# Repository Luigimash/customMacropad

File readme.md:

# Custom Macropad

A completely custom-built customizable macropad I built as a gift for a friend. Completed officially on March 11 2024.

Features:
- 3D printed enclosure
- Laser cut 1.5mm acrylic plate
- Custom PCB 
- QMK VIAL firmware 

All of my design files are collected within this repository. Some other items that you may need to purchase to complete this build:
- Standard Mechanical Keyboard Switches with a CherryMX footprint (used Wuque Studio Browns)
- SEED XIAO RP2040 Microcontroller
- 1N4148 Small Signal Switching Diodes
- EC11 (used Alps EC11E15244B2-ND)

Some tools I used:
- 3D Printers
- Laser Cutters
- AutoCAD for designing the acrylic plate
- Solidworks for designing the enclosure
- KiCAD for the circuit schematic and PCB gerbers

## Gallery

## Next Steps
- The rotary encoders are WAY too close to the keycaps, making it difficult to rotate (although it does thankfully actually rotate). They should be moved such that they are placed further away from the keycaps by at least 5mm or so.

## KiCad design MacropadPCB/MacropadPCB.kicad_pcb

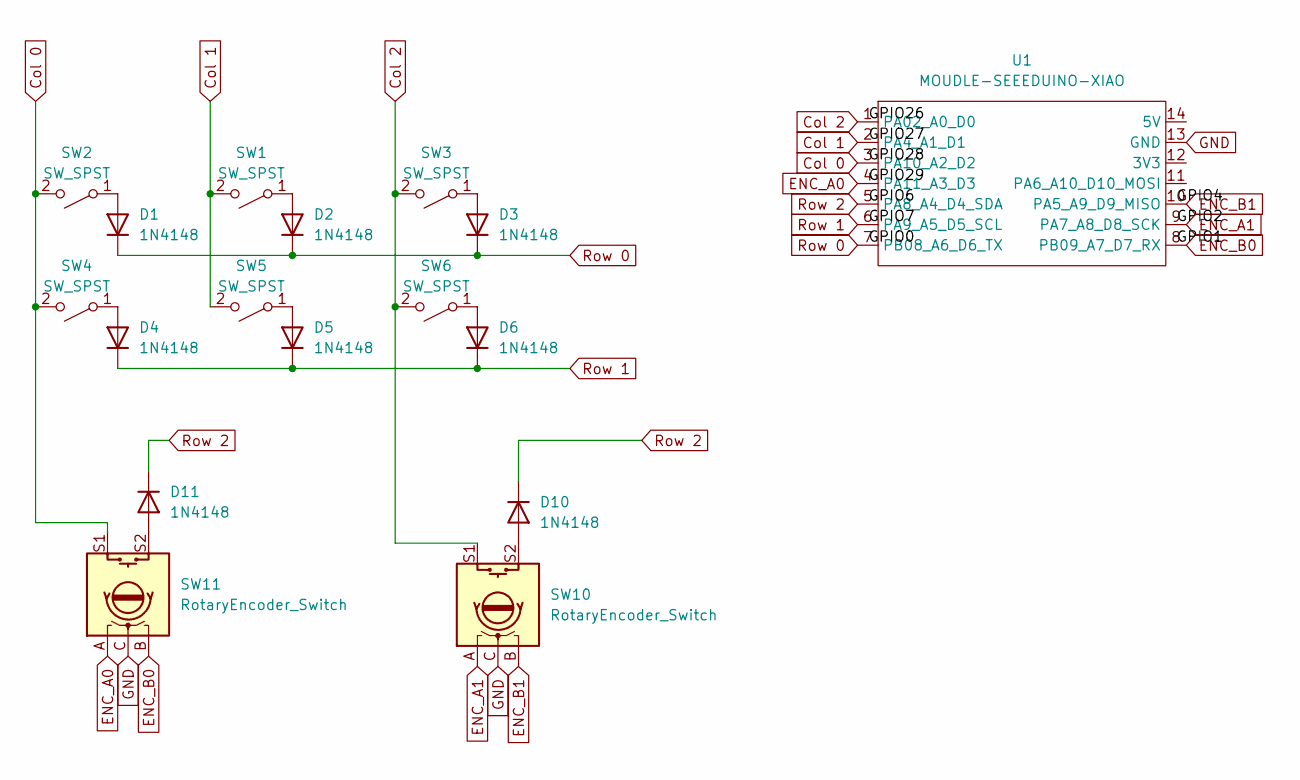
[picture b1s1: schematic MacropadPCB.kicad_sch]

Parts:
D1, D2, D3, D4, D5, D6, D10, D11: 1N4148; D_DO-35_SOD27_P7.62mm_Horizontal
SW1, SW2, SW3, SW4, SW5, SW6: SW_SPST; SW_Cherry_MX_1.00u_PCB
SW10, SW11: RotaryEncoder_Switch; RotaryEncoder_Alps_EC11E-Switch_Vertical_H20mm
U1: MOUDLE-SEEEDUINO-XIAO; MOUDLE14P-SMD-2.54-21X17.8MM

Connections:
Col 0: SW2.2 (B), SW4.2 (B), SW11.S1, U1.3 (PA10_A2_D2)
Col 1: SW1.2 (B), SW5.2 (B), U1.2 (PA4_A1_D1)
Col 2: SW3.2 (B), SW6.2 (B), SW10.S1, U1.1 (PA02_A0_D0)
ENC_A0: SW11.A, U1.4 (PA11_A3_D3)
ENC_A1: SW10.A, U1.9 (PA7_A8_D8_SCK)
ENC_B0: SW11.B, U1.8 (PB09_A7_D7_RX)
ENC_B1: SW10.B, U1.10 (PA5_A9_D9_MISO)
GND: SW10.C, SW11.C, U1.13 (GND)
unnamed: D1.2 (A), SW2.1 (A)
unnamed: D2.2 (A), SW1.1 (A)
unnamed: D3.2 (A), SW3.1 (A)
unnamed: D4.2 (A), SW4.1 (A)
unnamed: D5.2 (A), SW5.1 (A)
unnamed: D6.2 (A), SW6.1 (A)
unnamed: D10.2 (A), SW10.S2
unnamed: D11.2 (A), SW11.S2
Row 0: D1.1 (K), D2.1 (K), D3.1 (K), U1.7 (PB08_A6_D6_TX)
Row 1: D4.1 (K), D5.1 (K), D6.1 (K), U1.6 (PA9_A5_D5_SCL)
Row 2: D10.1 (K), D11.1 (K), U1.5 (PA8_A4_D4_SDA)

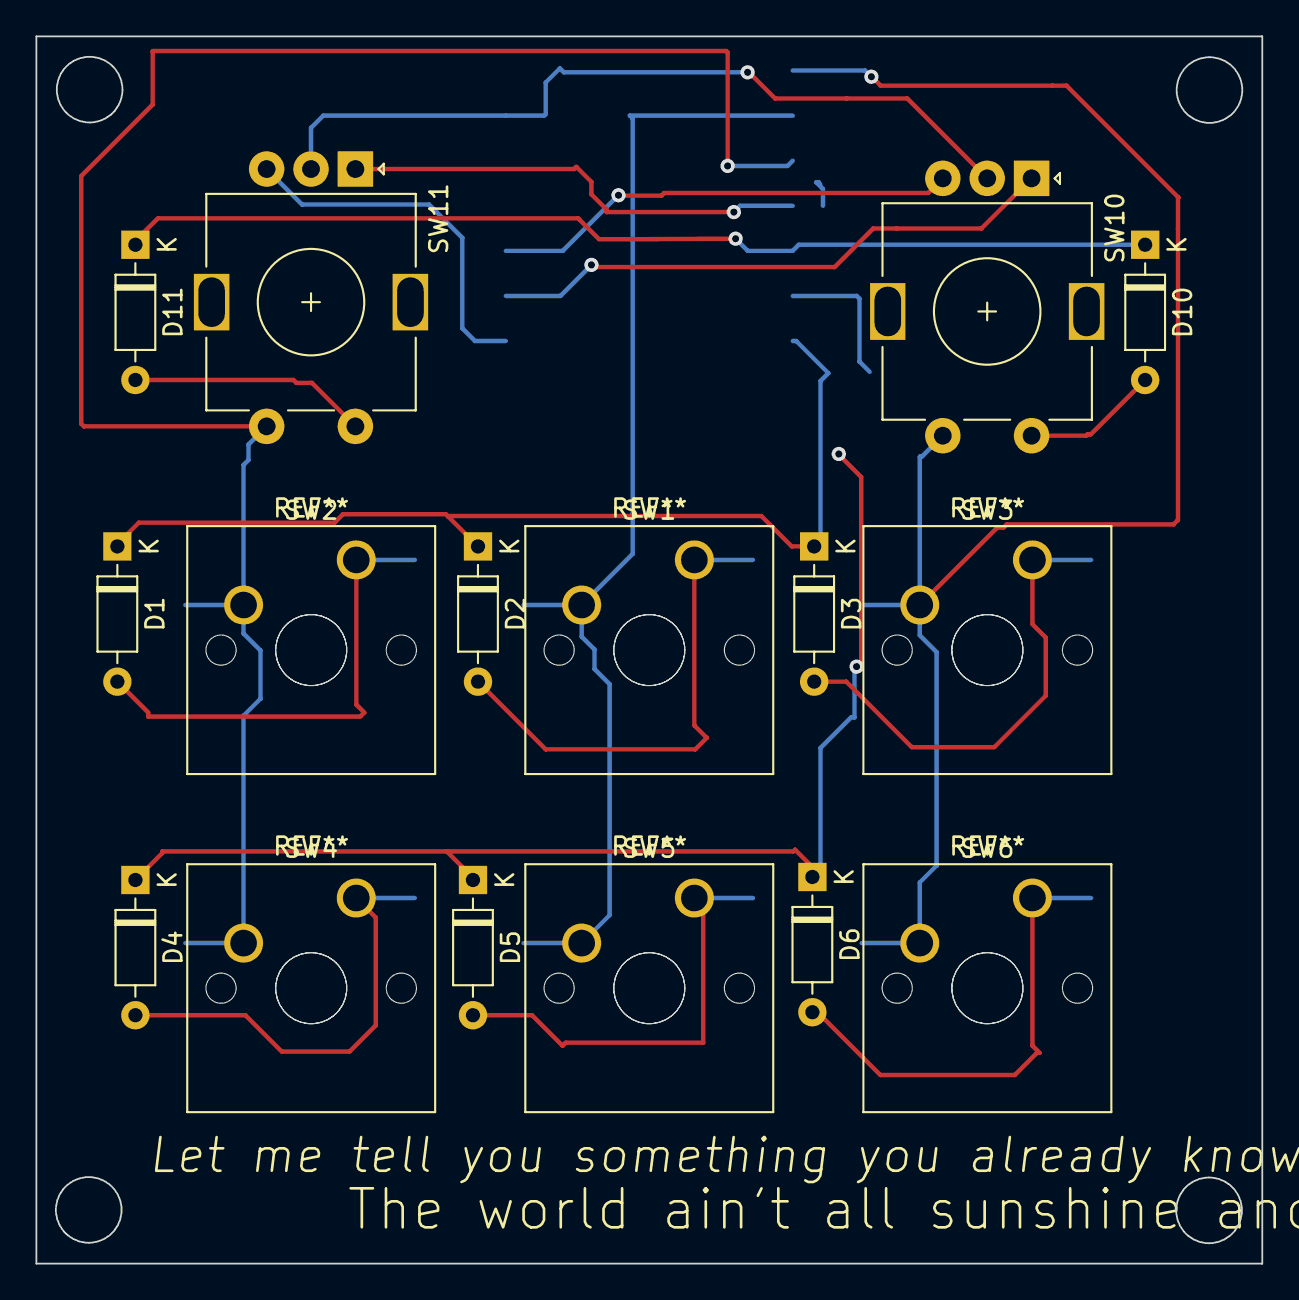
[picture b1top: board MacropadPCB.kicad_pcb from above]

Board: 2 copper layers, 69.1 x 69.1 mm, 17 parts (1 on the bottom side), 19 nets.

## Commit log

2024-03-13 Adding Readme and more media
2024-03-20 adding next steps
